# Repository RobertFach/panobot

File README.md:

PANOBOT: A Panorama robot, version 1

Panobot is a full automatic robot, which can be used to create Panoramas and Gigapixels with small and large cameras (like DSLRs). The camera is mounted on a turret to allow pan/tilt motion. After programming the capture parameters, the robot will start to rotate the camera, taking one (or multiple) pictures per position and making sure that the capture positions have enough overlap.

Panobot has the following menu features:
 * Scan
   * starts a scan
 * Sphere
   * starts a spherical scan (360x180)
 * Take picture
   * allows to manually take a picture, this is usefull for testing the camera trigger connection
 * Setup
   * Pan Left, Pan Right, Tilt Up, Tilt Down
     * defines the scan area of the panorama/gigapixel, the head will move while the range is defined, this is used for a normal scan
   * Image P-Delay
     * the longer, the more time the camera has to measure and (eventually focus, if not in manual camera mode), triggers focusing of camera
   * Image Delay
     * the delay it take for the camera to write the image to the card and/or the time it needs to stabilize the mechanical system due to rotating motion
   * Shutter Delay
     * how long the shutter will be pressed
   * Focal Length
     * the focal length which is currently by the camera
   * Horizontal& Vertical Overlap
     * defines the overlap between consecutive images, a value between 30% and 50% makes sense, usually depends on the capture situation
   * Crop factor
     * in combination with the focal length, can be used to calculate field of view, which is required for horizontal&vertical overlap

Required Hardware:
 * 3d printed parts
   * Please have a look at [Panobot at Thingiverse](https://www.thingiverse.com/thing:2503118) to find out the parts that need to be printed
 * mechanical parts
   * some screws, washers, nuts M3, M4
   * some bearings 608 (around 10)
   * some rods 8mm (for structure and as axis)
 * electronic parts
   * 2 stepper motors Nema17, like 42BYGHM810
   * Arduino Mega 2560
   * Reprap Full Graphic SmartLCD with clickencoder
   * the controller PCB in version 1.1.0, which consists of two stepper drivers A4988 and two optocopplers; you can build your own pcb (see pcb folder) or get one...

Required Software:
   * install atom editor
     * https://atom.io/ -> install deb
   * follow steps on http://platformio.org/get-started/ide?install=atom
     * install platformio-ide package inside atom
   * code completion
     * apt-get install clang

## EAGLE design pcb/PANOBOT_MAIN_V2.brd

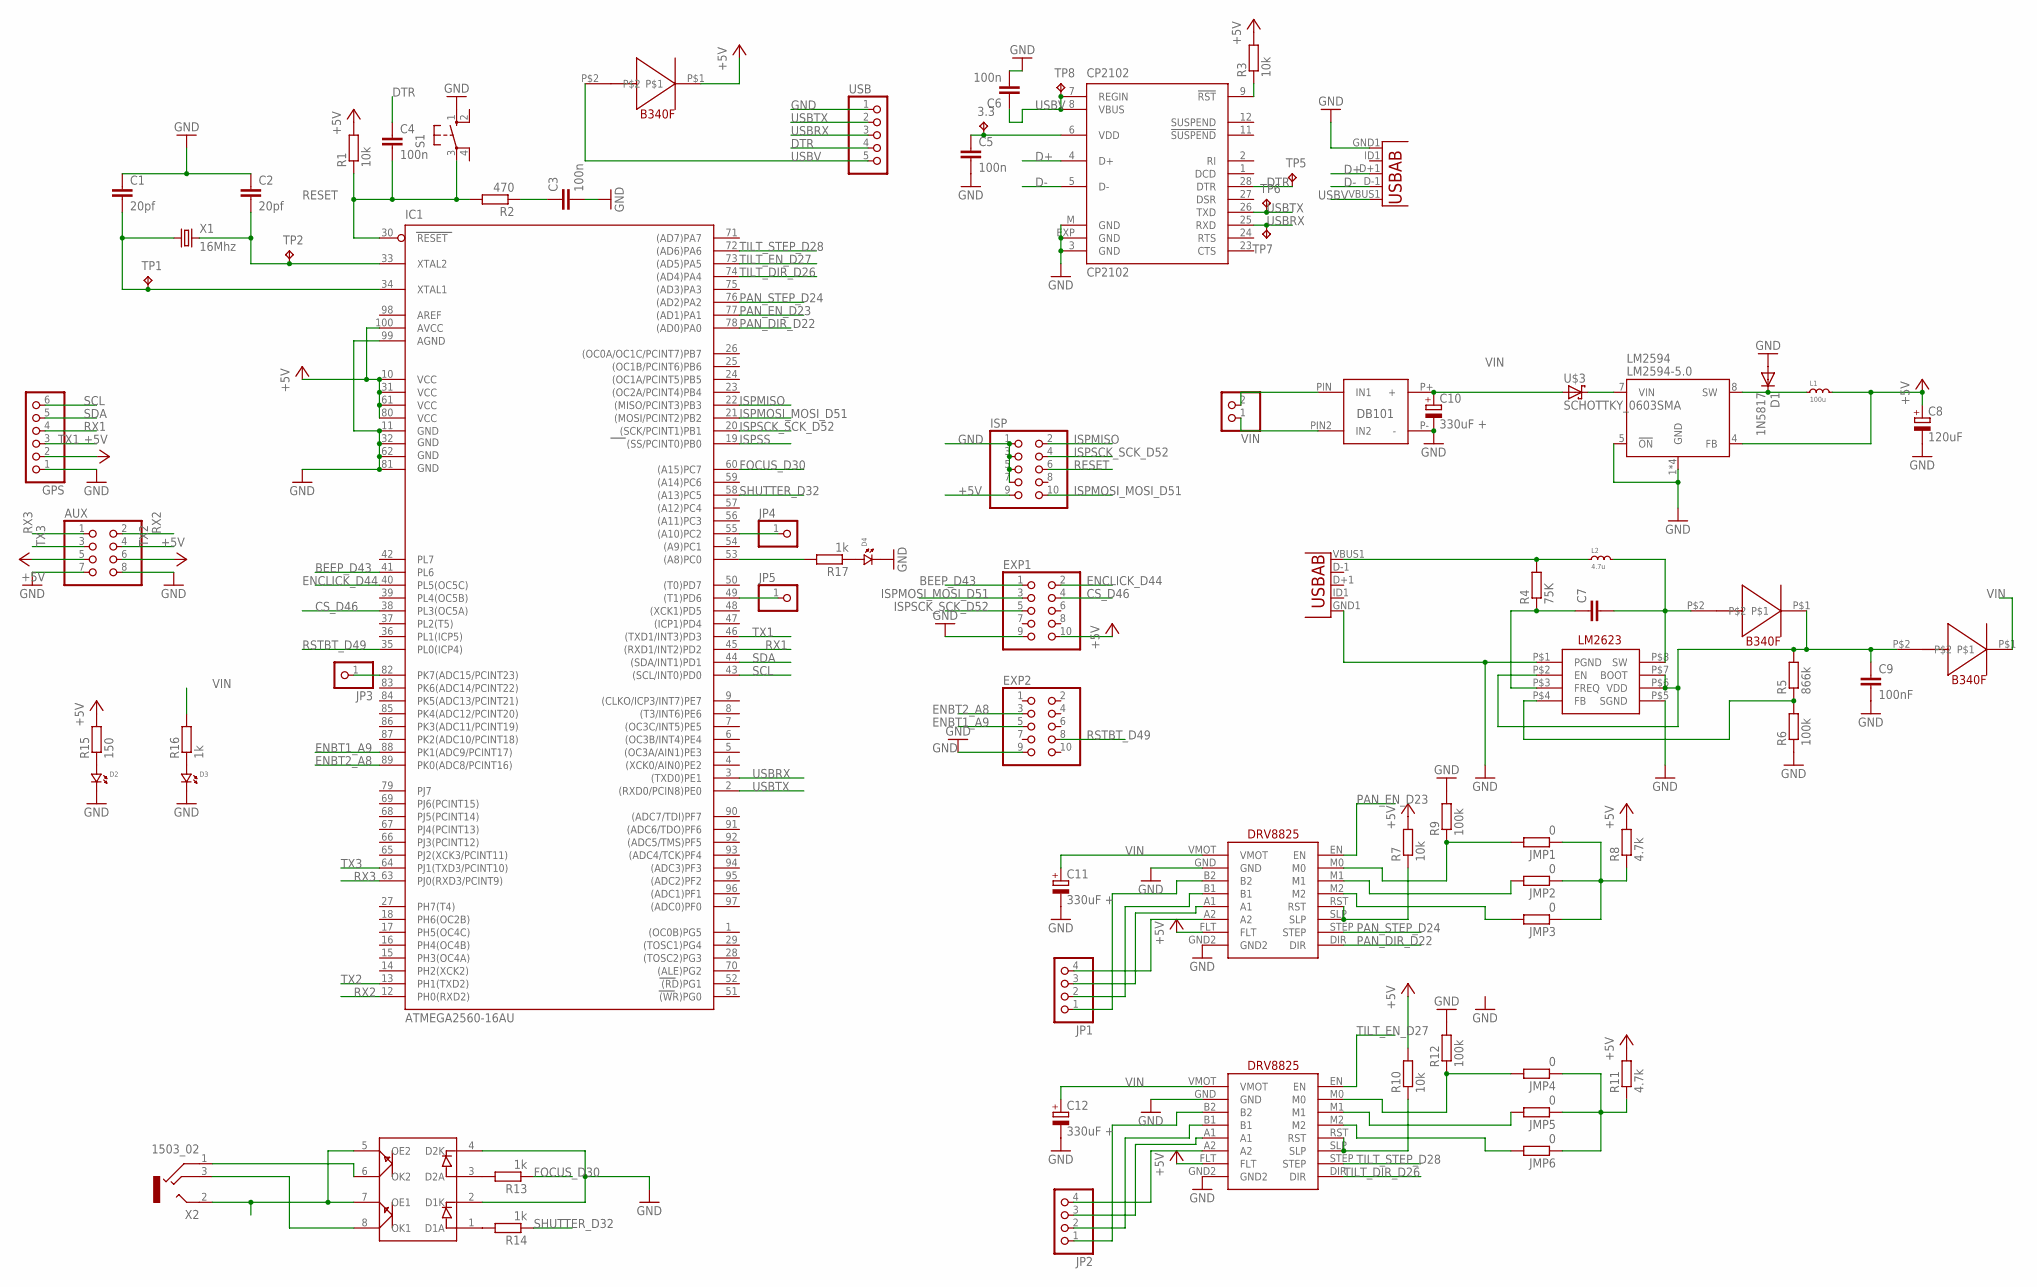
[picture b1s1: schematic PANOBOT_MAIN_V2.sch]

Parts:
3.3: TPTP16R; TP16R
AUX: PINHD-2X4; 2X04
C1, C2: 20pf; C0603K
C3, C4, C5, C6: 100n; C0805
C7: C-EUC0603; C0603
C8: 120uF; 153CLV-0605
C9: 100nF; C025-030X050
C10, C11, C12: 330uF +; SANYO-OSCON_F13
CP2102: CP2102; MLP28
D1: 1N5817; DO41-10
D2, D3, D4: LED.0805; 0805.LED
EXP1, EXP2: PINHD-2X5; 2X05
GPS: PINHD-1X6; 1X06
IC1: ATMEGA2560-16AU; TQFP100
ISP: PINHD-2X5; 2X05
JMP1, JMP2, JMP3, JMP4, JMP5, JMP6: 0; R0805
JP1, JP2: PINHD-1X4; 1X04
JP3, JP4, JP5: PINHD-1X1; 1X01
L1: 100u; HPINDUCTOR100
L2: 4.7u; HPINDUCOR
LM2594: LM2594-5.0; SO08
LM2623: LM2623; MINI-SO-8
R1, R3, R7, R10: 10k; R0805
R2: 470; R0805
R4: 75K; R0805
R5: 866k; R0805
R6, R9, R12: 100k; R0805
R8, R11: 4.7k; R0805
R13, R14, R16, R17: 1k; R0805
R15: 150; R0805
S1: 10-XX; B3F-10XX
TP1, TP2, TP5, TP6, TP7, TP8: TPTP16R; TP16R
U1, U2: USB""; USB-MICRO-SMD
U$1, U$4, U$5: B340FSCHOTTKY; SMC
U$2: DB101_BRUECKENGLEICHRICHTER; DB101_PACK
U$3: SCHOTTKY_0603SMA; SMA
U$6, U$7: DRV8825; DRV8825POLULOU
U$8: LTV827SMD8; SMD8
USB: PINHD-1X5; 1X05
VIN: PINHD-1X2; 1X02
X1: 16Mhz; HC49-4-HSMX
X2: 1503_02

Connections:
+5V: AUX.5, AUX.6, C8.+, EXP1.10, GPS.2, IC1.10 (VCC), IC1.31 (VCC1), IC1.61 (VCC2), IC1.80 (VCC3), IC1.100 (AVCC), ISP.9, L1.P$2 (2), LM2594.4 (FB), R1.2, R3.2, R7.2, R8.2, R10.2, R11.2, R15.2, U$1.P$1, U$6.FLT, U$7.FLT
+5VUSBPWR: L2.P$1 (1), R4.2, U2.VBUS1 (VBUS)
BEEP_D43: EXP1.1, IC1.41 (PL6)
CS_D46: EXP1.4, IC1.38 (PL3(OC5A))
D+: CP2102.4 (D+), U1.D+1 (D+)
D-: CP2102.5 (D-), U1.D-1 (D-)
DTR: C4.1, CP2102.28 (DTR), TP5.TP, USB.4
ENBT1_A9: EXP2.5, IC1.88 (PK1(ADC9/PCINT17))
ENBT2_A8: EXP2.3, IC1.89 (PK0(ADC8/PCINT16))
ENCLICK_D44: EXP1.2, IC1.40 (PL5(OC5C))
FOCUS_D30: IC1.60 ((A15)PC7), R13.1
GND: AUX.7, AUX.8, C1.1, C2.1, C3.2, C5.2, C6.2, C8.-, C9.2, C10.-, C11.-, C12.-, CP2102.3 (GND), CP2102.EXP (GND), CP2102.M (GND), D1.A, D2.P$2 (2), D3.P$2 (2), D4.P$2 (2), EXP1.9, EXP2.9, GPS.1, IC1.11 (GND), IC1.32 (GND1), IC1.62 (GND2), IC1.81 (GND3), IC1.99 (AGND), ISP.1, ISP.3, ISP.5, ISP.7, LM2594.1 (GND), LM2594.2 (GND), LM2594.3 (GND), LM2594.5 (!ON!), LM2594.6 (GND), LM2623.P$1 (PGND), LM2623.P$5 (SGND), R6.1, R9.2, R12.2, S1.1 (S), U1.GND1 (GND), U2.GND1 (GND), U$2.P- (-), U$6.GND, U$6.GND2, U$7.GND, U$7.GND2, U$8.2 (D1K), U$8.4 (D2K), USB.1
ISPMISO: IC1.22 ((MISO/PCINT3)PB3), ISP.2
ISPMOSI_MOSI_D51: EXP1.3, IC1.21 ((MOSI/PCINT2)PB2), ISP.10
ISPSCK_SCK_D52: EXP1.5, IC1.20 ((SCK/PCINT1)PB1), ISP.4
ISPSS: IC1.19 ((SS/PCINT0)PB0)
unnamed: 3.3.TP, C5.1, CP2102.6 (VDD)
unnamed: CP2102.9 (!RST), R3.1
unnamed: C3.1, R2.1
unnamed: LM2623.P$4 (FB), R5.1, R6.2
unnamed: C7.1, LM2623.P$3 (FREQ), R4.1
unnamed: D1.C, L1.P$1 (1), LM2594.8 (SW)
unnamed: JMP1.2, R9.1, U$6.M0
unnamed: C7.2, L2.P$2 (2), LM2623.P$8 (SW), U$4.P$2
unnamed: JMP2.2, U$6.M1
unnamed: C9.1, LM2623.P$2 (EN), LM2623.P$6 (VDD), LM2623.P$7 (BOOT), R5.2, U$4.P$1, U$5.P$2
unnamed: JMP3.2, U$6.M2
unnamed: JMP1.1, JMP2.1, JMP3.1, R8.1
unnamed: JP1.1, U$6.B2
unnamed: JP1.2, U$6.B1
unnamed: JP1.3, U$6.A1
unnamed: JP1.4, U$6.A2
unnamed: JMP4.2, R12.1, U$7.M0
unnamed: JMP5.2, U$7.M1
unnamed: JMP6.2, U$7.M2
unnamed: JMP4.1, JMP5.1, JMP6.1, R11.1
unnamed: JP2.1, U$7.B2
unnamed: JP2.2, U$7.B1
unnamed: JP2.3, U$7.A1
unnamed: JP2.4, U$7.A2
unnamed: R13.2, U$8.3 (D2A)
unnamed: R14.2, U$8.1 (D1A)
unnamed: U$8.6 (OK2), X2.1
unnamed: U$8.8 (OK1), X2.3
unnamed: U$8.5 (OE2), U$8.7 (OE1), X2.2
unnamed: U$2.PIN (IN1), VIN.2
unnamed: U$2.PIN2 (IN2), VIN.1
unnamed: IC1.82 (PK7(ADC15/PCINT23)), JP3.1
unnamed: IC1.55 ((A10)PC2), JP4.1
unnamed: IC1.49 ((T1)PD6), JP5.1
unnamed: D2.P$1 (1), R15.1
unnamed: D3.P$1 (1), R16.1
unnamed: D4.P$1 (1), R17.1
unnamed: IC1.53 ((A8)PC0), R17.2
unnamed: LM2594.7 (VIN), U$3.P$1 (C)
PAN_DIR_D22: IC1.78 ((AD0)PA0), U$6.DIR
PAN_EN_D23: IC1.77 ((AD1)PA1), U$6.EN
PAN_STEP_D24: IC1.76 ((AD2)PA2), U$6.STEP
RESET: C4.2, IC1.30 (RESET), ISP.6, R1.1, R2.2, S1.3
RESET1: R7.1, U$6.RST, U$6.SLP
RESET2: R10.1, U$7.RST, U$7.SLP
RSTBT_D49: EXP2.8, IC1.35 (PL0(ICP4))
RX1: GPS.4, IC1.45 ((RXD1/INT2)PD2)
RX2: AUX.2, IC1.12 (PH0(RXD2))
RX3: AUX.1, IC1.63 (PJ0(RXD3/PCINT9))
SCL: GPS.6, IC1.43 ((SCL/INT0)PD0)
SDA: GPS.5, IC1.44 ((SDA/INT1)PD1)
SHUTTER_D32: IC1.58 ((A13)PC5), R14.1
TILT_DIR_D26: IC1.74 ((AD4)PA4), U$7.DIR
TILT_EN_D27: IC1.73 ((AD5)PA5), U$7.EN
TILT_STEP_D28: IC1.72 ((AD6)PA6), U$7.STEP
TX1: GPS.3, IC1.46 ((TXD1/INT3)PD3)
TX2: AUX.4, IC1.13 (PH1(TXD2))
TX3: AUX.3, IC1.64 (PJ1(TXD3/PCINT10))
USBRX: CP2102.25 (RXD), IC1.3 ((TXD0)PE1), TP7.TP, USB.3
USBTX: CP2102.26 (TXD), IC1.2 ((RXD0/PCIN8)PE0), TP6.TP, USB.2
USBV: C6.1, CP2102.7 (REGIN), CP2102.8 (VBUS), TP8.TP, U1.VBUS1 (VBUS), U$1.P$2, USB.5
VIN: C10.+, C11.+, C12.+, R16.2, U$2.P+ (+), U$3.P$2 (A), U$5.P$1, U$6.VMOT, U$7.VMOT
XTAL1: C1.2, IC1.34 (XTAL1), TP1.TP, X1.1
XTAL2: C2.2, IC1.33 (XTAL2), TP2.TP, X1.2

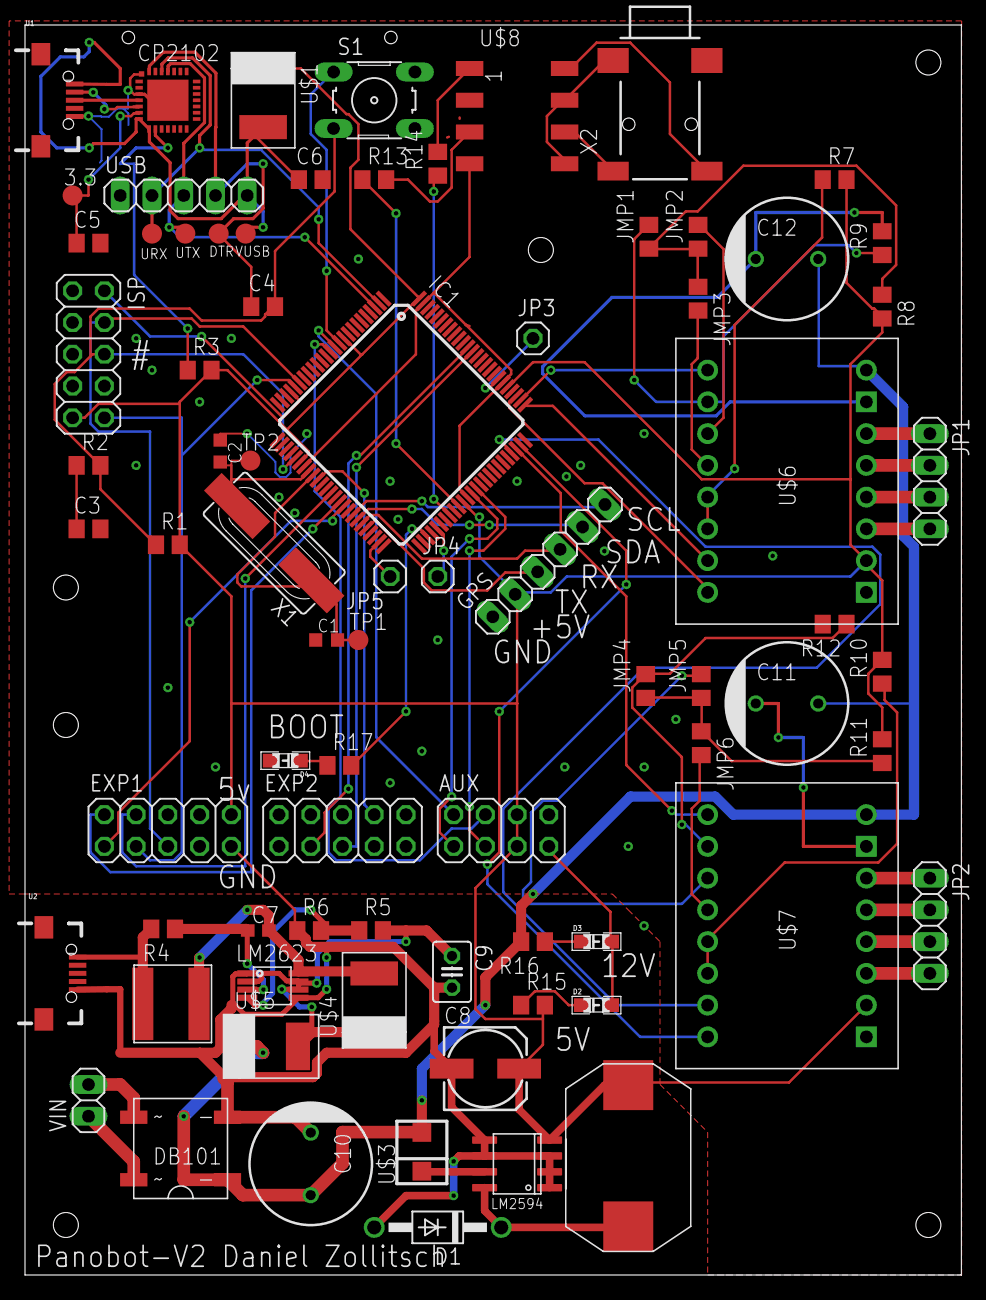
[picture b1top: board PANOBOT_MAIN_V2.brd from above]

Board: 2 copper layers, 74.9 x 100.0 mm, 77 parts (0 on the bottom side), 79 nets.

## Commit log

2017-07-06 add README
2017-07-06 added gigascan construction files
2017-07-06 added hardware wiring pictures for stepstick driver and canon remote controller
2017-07-06 added megamount print and initial software
2017-07-07 adding MCAD
2017-07-07 added camquickmount
2017-07-07 added quickmount clamp for camera quickmount
2017-07-08 added MCAD as submodule
2017-07-08 added AccelStepper and Arduino LCD Menu, updated submodule refs
2017-07-08 added Menu and Stepper Library, included Menu & Stepper Testcode into main file
2017-07-08 implemented PAN scan, added primitive take picture function
2017-07-08 added/enabled tilt stepper, added tilt step/scan setup
2017-07-10 extended scan to alsoscan rows (tilt), added Picture Pre and Post Delay
2017-07-15 modified quickcam mount to match mount of andoer professionals mount
2017-07-15 added microstepping capabilities
2017-07-15 added andoer cam quickmount model (stl)
2017-07-15 rewrite of scanner to use focal length, crop¸ image overlap to calculate a scan pattern; scanner has been rewritten, added also debugging via serial interface
2017-07-27 refactored for arduino-mk
2017-08-08 removed submodules
2017-08-08 Squashed 'software/gigascan/libraries/AccelStepper/' content from commit 85c9c97
    git-subtree-dir: software/gigascan/libraries/AccelStepper
    git-subtree-split: 85c9c975b911a2b77eba99a7531d14675cc6e67a
2017-08-08 Squashed 'software/gigascan/libraries/Arduino_LCD_Menu/' content from commit 5a81bfe
    git-subtree-dir: software/gigascan/libraries/Arduino_LCD_Menu
    git-subtree-split: 5a81bfea3451c79112b9a7ddb2496e45b320413a
2017-08-08 fixed arduino header not found issue
2017-08-08 Squashed 'software/gigascan/libraries/USB_Host_Shield_2.0/' content from commit fb47645
    git-subtree-dir: software/gigascan/libraries/USB_Host_Shield_2.0
    git-subtree-split: fb47645ea79b084a66e85b36c0fe301c63efb9e5
2017-08-08 Squashed 'software/gigascan/libraries/PTP_2.0/' content from commit edea776
    git-subtree-dir: software/gigascan/libraries/PTP_2.0
    git-subtree-split: edea7765054faba83e69edf8f7e5ae1bf94a5516
2017-08-09 added Makefile for EOSCapture test
2017-08-09 Squashed 'software/gigascan/libraries/USB_Host_Shield/' content from commit 880773a
    git-subtree-dir: software/gigascan/libraries/USB_Host_Shield
    git-subtree-split: 880773a1cfd5a521f97493b0e4de7f243a2c2925
2017-08-09 Squashed 'software/gigascan/libraries/Arduino_Camera_Control/' content from commit 4f5b1bf
    git-subtree-dir: software/gigascan/libraries/Arduino_Camera_Control
    git-subtree-split: 4f5b1bf438d160ee8836b36b7482e28c9e0700b0
2017-08-09 added USB Host Shield & PTP version 1.0, fixed arduino > 1.0 compatibility
2017-08-09 fixed horizontal & vertical overlap error
2017-08-09 set repeat debounce delay to 250ms to improve useability
2017-08-10 changed tilt steps per deg to match mechanics, leasons learned - calibrate before :)
2017-08-10 make pan steps increment depending from focal length (increment by resulting images)
2017-08-31 removed u8glib
2017-08-31 replaced zig-zag scan by line scanning
2017-08-31 Squashed 'software/gigascan/libraries/u8g2/' content from commit cf9f713
    git-subtree-dir: software/gigascan/libraries/u8g2
    git-subtree-split: cf9f7134337fa6ad83f3c4143a738a120c9d3775
2017-09-01 added smart lcd case
2017-09-01 added wiring diagrams for smart lcd
2017-09-01 controller case, bottom part
2017-09-09 arranged parts for printing
2017-09-09 refactored code to platformio IDE/tooling, also added u8g2, refactored code to use Smart Full Graphics LCD with Clickencoder
2017-09-12 rerouted smartlcd to use hardware SPI and moved encoder away from SPI pins :/
2017-09-14 gui changes: added live status during scanning & scanner configuration update in status during configuration
2017-09-15 added Mega2560 pinout
2017-09-15 removed libraries folder, added PTP lib
2017-09-16 updated configuration section, fixed issue with displaying status message, reorganized/commented code
2017-09-16 added license and readme
2017-09-16 moved LICENSE and documentation a few levels up
2017-09-18 added simple version of controller box, its not fault free
2017-10-09 added hardware setup menu for pan/tilt steps, speed, accel settings
2017-10-29 added a schema for the electronic
2017-12-07 updated schema files to match prototype pcb routing
2017-12-12 increased accel & speed settings, added update function to menu
2017-12-14 refactored scanner to use a state machine with non blocking delays, first step toward usb trigger
2017-12-16 implemented spherical mode
2017-12-23 updated schematic and added pcb layout
2017-12-23 added spherical scan mode to readme, updated pcb section
2018-01-03 added an improved version of the tilt side, which has larger gears
2018-01-27 implemented a splashscreen (with fractals)
2018-01-28 added eeprom, user configuration can now be stored and restored from eeprom
2018-01-28 fixed updateScanner printout
2018-02-26 added pcb images for wiki
2018-02-26 added pcb backside picture
